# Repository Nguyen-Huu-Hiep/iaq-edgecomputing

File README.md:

# Hệ Thống Giám Sát Chất Lượng Không Khí Trong Nhà Dựa Trên Edge Computing

## Tổng Quan

Đề tài xây dựng hệ thống giám sát chất lượng không khí trong nhà (Indoor Air Quality - IAQ) dựa trên công nghệ Edge Computing và Internet of Things (IoT). Hệ thống sử dụng vi điều khiển ESP32 kết hợp với nhiều cảm biến môi trường để thu thập, xử lý và giám sát các thông số chất lượng không khí theo thời gian thực.

Khác với các hệ thống IoT truyền thống phụ thuộc hoàn toàn vào điện toán đám mây, hệ thống này thực hiện phần lớn quá trình xử lý dữ liệu ngay trên thiết bị biên (Edge Device). Các dữ liệu từ cảm biến được lọc nhiễu, phân tích và tính toán chỉ số chất lượng không khí (AQI) trước khi được gửi lên máy chủ để lưu trữ và trực quan hóa.

Hệ thống có khả năng giám sát liên tục các thông số như bụi mịn PM2.5, PM10, nồng độ CO₂, TVOC, nhiệt độ và độ ẩm. Chỉ số AQI được tính toán trực tiếp trên ESP32 theo tiêu chuẩn US EPA, giúp giảm độ trễ và đảm bảo khả năng cảnh báo kịp thời khi chất lượng không khí suy giảm.

---

## Chức Năng Chính

- Giám sát chất lượng không khí theo thời gian thực
- Đo nồng độ bụi PM2.5 và PM10
- Đo nồng độ khí CO₂
- Đo chỉ số TVOC
- Đo nhiệt độ và độ ẩm môi trường
- Tính toán chỉ số AQI tại thiết bị Edge
- Hiển thị dữ liệu trên màn hình TFT
- Lọc nhiễu bằng Median Filter và Kalman Filter
- Kết nối WiFi và tự động kết nối lại khi mất mạng
- Đồng bộ dữ liệu lên nền tảng Supabase
- Hỗ trợ cập nhật firmware OTA (Over-The-Air)
- Cảnh báo cục bộ khi chất lượng không khí vượt ngưỡng
- Cấu hình hệ thống thông qua giao diện Web

---

## Kiến Trúc Hệ Thống

## Phần Cứng Sử Dụng

- ESP32 Development Board
- Cảm biến bụi PMS5003/PMS7003
- Cảm biến CO₂ Sensirion SCD4x
- Cảm biến TVOC CCS811
- Màn hình TFT ST7789
- Hệ thống mạng WiFi

---

## Mô Hình Edge Computing

Hệ thống được thiết kế theo kiến trúc Edge Computing, trong đó ESP32 đóng vai trò là nút xử lý biên (Edge Node).

Các tác vụ được thực hiện trực tiếp trên ESP32 bao gồm:

- Thu thập dữ liệu cảm biến
- Kiểm tra tính hợp lệ của dữ liệu
- Lọc nhiễu tín hiệu
- Tính toán AQI
- Phát hiện trạng thái bất thường
- Kích hoạt cảnh báo cục bộ

Nhờ đó hệ thống mang lại các lợi ích:

- Giảm độ trễ xử lý
- Giảm lưu lượng truyền dữ liệu lên Cloud
- Giảm tải cho máy chủ
- Tăng tính ổn định khi mất kết nối Internet
- Đảm bảo khả năng cảnh báo theo thời gian thực

---

## Xử Lý Dữ Liệu

### Median Filter

Được sử dụng để loại bỏ các giá trị nhiễu đột biến từ cảm biến.

### Kalman Filter

Được sử dụng để làm mượt dữ liệu đo, tăng độ ổn định và độ tin cậy của kết quả.

### Tính Toán AQI

Chỉ số chất lượng không khí AQI được tính toán trực tiếp trên ESP32 dựa trên nồng độ PM2.5 theo tiêu chuẩn của Cơ quan Bảo vệ Môi trường Hoa Kỳ (US EPA).

---

## Kết Nối Đám Mây

Dữ liệu sau khi được xử lý tại Edge sẽ được gửi lên nền tảng Supabase thông qua giao thức HTTPS để:

- Lưu trữ lịch sử dữ liệu
- Phân tích xu hướng chất lượng không khí
- Hiển thị trên Dashboard giám sát
- Hỗ trợ truy cập từ xa

---

## Ứng Dụng

Hệ thống có thể được triển khai tại:

- Nhà ở thông minh (Smart Home)
- Lớp học
- Văn phòng
- Phòng thí nghiệm
- Bệnh viện
- Nhà xưởng sản xuất
- Các không gian kín cần giám sát chất lượng không khí

---

## Công Nghệ Sử Dụng

- ESP32
- Edge Computing
- Internet of Things (IoT)
- Supabase
- WiFi Manager
- OTA Firmware Update
- HTTP/HTTPS Communication
- AQI Calculation (US EPA Standard)

---

## Tác Giả

**Nguyễn Hữu Hiệp**

Ngành Kỹ thuật Tin học Công nghiệp

**Đồ án tốt nghiệp: Hệ thống giám sát chất lượng không khí trong nhà dựa trên Edge Computing và IoT**

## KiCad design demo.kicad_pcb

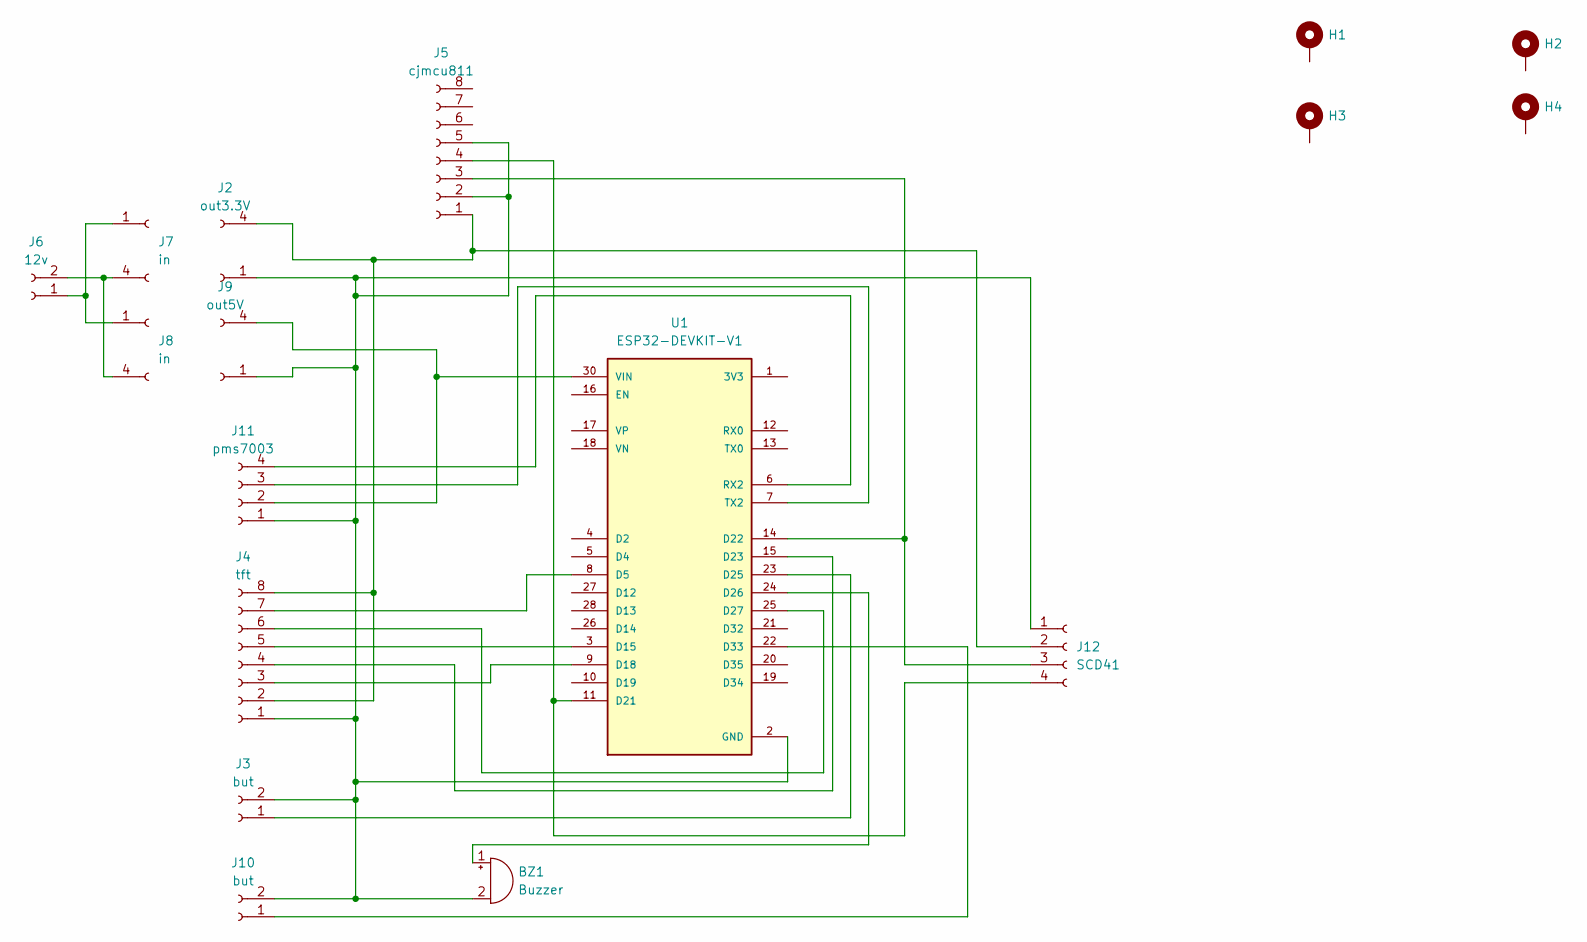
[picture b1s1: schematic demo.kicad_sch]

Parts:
BZ1: Buzzer; Buzzer_12x9.5RM7.6
H1, H2, H3, H4: MountingHole_Pad; MountingHole_2.2mm_M2_Pad_Via
J2: out3.3V; PinSocket_1x04_P2.54mm_Vertical
J3, J10: but; JST_PH_B2B-PH-K_1x02_P2.00mm_Vertical
J4: tft; JST_PH_B8B-PH-K_1x08_P2.00mm_Vertical
J5: cjmcu811; PinSocket_1x08_P2.54mm_Vertical
J6: 12v; JST_PH_B2B-PH-K_1x02_P2.00mm_Vertical
J7, J8: in; PinSocket_1x04_P2.54mm_Vertical
J9: out5V; PinSocket_1x04_P2.54mm_Vertical
J11: pms7003; JST_PH_B4B-PH-K_1x04_P2.00mm_Vertical
J12: SCD41; PinSocket_1x04_P2.54mm_Vertical
U1: ESP32-DEVKIT-V1; MODULE_ESP32_DEVKIT_V1; PARTREV N/A

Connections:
GND: BZ1.2 (-), J2.1, J3.2, J4.1, J5.2, J5.5, J9.1, J10.2, J11.1, J12.1, U1.2 (GND), U1.29 (GND)
unnamed: BZ1.1 (+), U1.24 (D26)
unnamed: J3.1, U1.23 (D25)
unnamed: J4.3, U1.9 (D18)
unnamed: J4.4, U1.15 (D23)
unnamed: J4.5, U1.3 (D15)
unnamed: J4.6, U1.25 (D27)
unnamed: J4.7, U1.8 (D5)
unnamed: J6.1, J7.1, J8.1
unnamed: J6.2, J7.4, J8.4
unnamed: J10.1, U1.22 (D33)
unnamed: J9.4, J11.2, U1.30 (VIN)
unnamed: J11.3, U1.7 (TX2)
unnamed: J11.4, U1.6 (RX2)
unnamed: J2.4, J4.2, J4.8, J5.1, J12.2
unnamed: J5.3, J12.3, U1.14 (D22)
unnamed: J5.4, J12.4, U1.11 (D21)

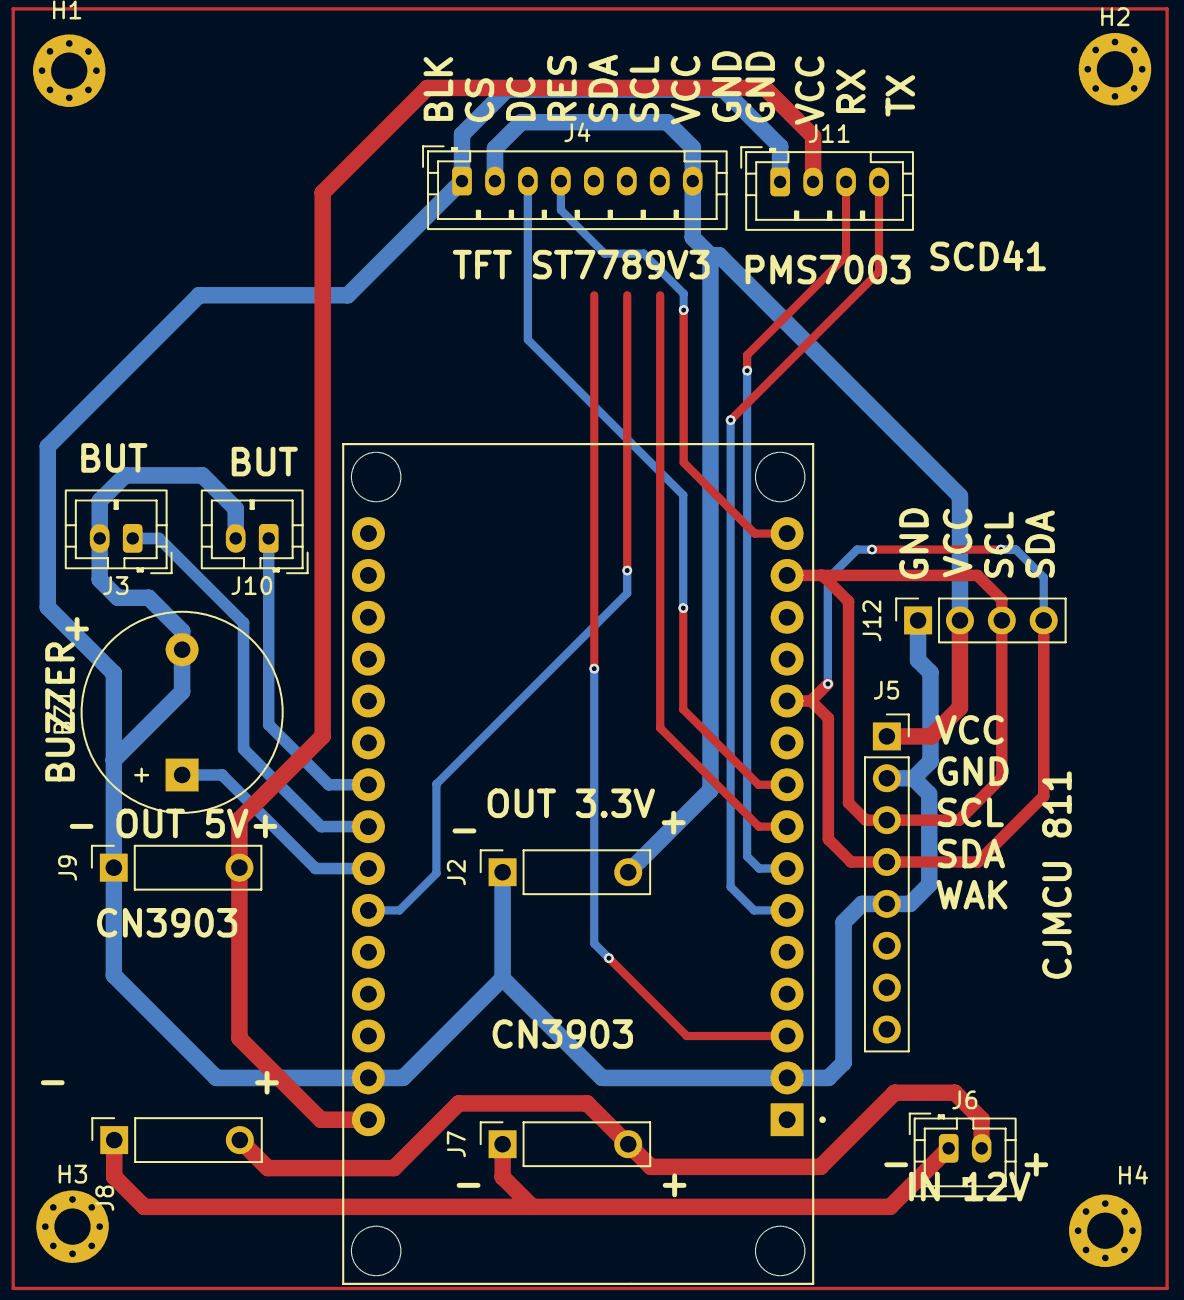
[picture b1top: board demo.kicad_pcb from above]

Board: 2 copper layers, 17 parts (0 on the bottom side), 17 nets.

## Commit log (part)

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2026-06-25 Create Build
